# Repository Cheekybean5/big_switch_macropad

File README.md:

# Big_Switch_Pad

BIG SWITCH MACROPAD is a custom macropad featuring a 2×4 cluster of ISO Enter keys stacked above a 1×6 row of 1u keys. Looming over the layout is a Kailh Big Switch that serves as the visual and functional centerpiece of the board. The pad runs QMK Firmware and is powered by an RP2040 microcontroller.

## Features:

- KAILH BIG SWITCH

- 8 x ISO ENTER Keys

- 6 x 1u Keys

- QMK Firmware

- 3d Printed Case

## CAD Model:

The main case section fits together using M3 x 16mm bolts and M3x5mmx4mm heatset inserts. 
The big switch housing is connected to main body using 6mm Diameter x 1.5mm magnets.

Here are some renders of the assembled case:

Case designed in Fusion360.

## PCB

PCB designed in KiCad. The Diode and Through-hole near the top must be handwired to the big switch.

Schematic:

PCB:

## Firmware

This project utilizes [QMK](https://qmk.fm/) firmware.

Here is the Default Keymap and Keycodes Assigned to it:

- The Big Switch acts as a large "off button" and is wired into the Matrix

## BOM:

Here is the list of parts required for this project:

- 14x Cherry MX switches

- 1x Kailh Big Switch (available at Novelkeys)

- 6x 1u Keycaps (any profile)

- 8x ISO Enter Keys

- 8x 2u Stabilizers (Semi-optional)

- 1x Seeed XIAO RP2040

- 2x Hookup Wire Segments (Approx. 6 inches each)

- 4x 6mm Diameter x 1.5mm Height Magnets

- 15x Through-hole 1N4148 Diodes

-  M3x16mm bolts

- M3x5mx4mm heatset inserts

- 1x Case (3 printed parts)

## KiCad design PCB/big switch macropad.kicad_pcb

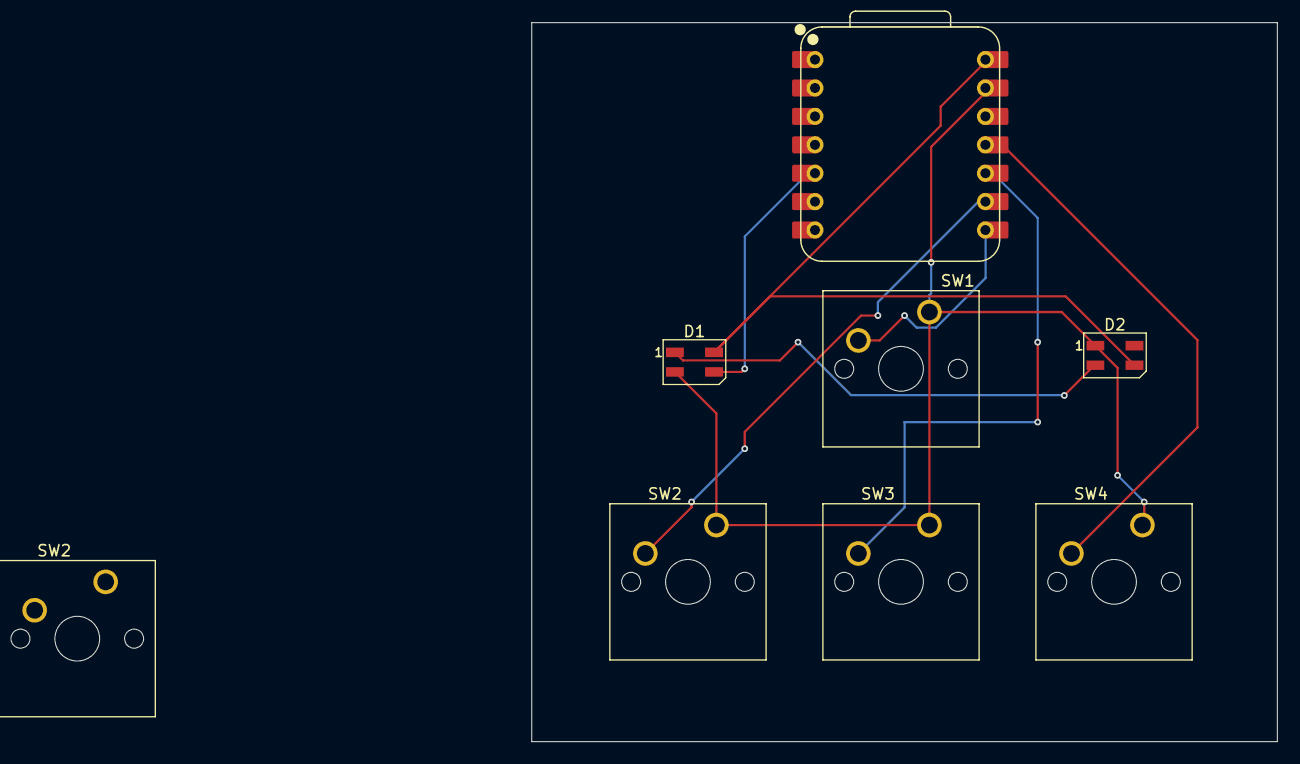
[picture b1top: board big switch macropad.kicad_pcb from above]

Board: 2 copper layers, 66.7 x 64.3 mm, 8 parts (0 on the bottom side), 8 nets.

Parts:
D1: SK6812MINI; LED_SK6812MINI_PLCC4_3.5x3.5mm_P1.75mm
D2: SK6812; LED_SK6812MINI_PLCC4_3.5x3.5mm_P1.75mm
SW1, SW2, SW2#2, SW3, SW4: SW_Push; SW_Cherry_MX_1.00u_PCB
U1: XIAO-RP2040-DIP

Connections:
+5V: D1.4 (VDD), D2.3 (VDD), U1.14 (VBUS)
GND: D1.2 (VSS), D2.1 (VSS), SW1.1, SW2#2.1, SW3.1, SW4.1, U1.13 (GND)
unnamed: D1.3 (DIN), U1.5 (GPIO6/SDA)
unnamed: D1.1 (DOUT), D2.2 (DIN)
unnamed: SW1.2, U1.8 (GPIO1/RX)
unnamed: SW2#2.2, U1.9 (GPIO2/SCK)
unnamed: SW4.2, U1.11 (GPIO3/MOSI)
unnamed: SW3.2, U1.10 (GPIO4/MISO)

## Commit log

2026-01-19 Add initial files
2026-01-19 Add default keymap image
    for readme
2026-01-19 Rename Default Keymap Assignments.png to default_keymap_assignments
2026-01-19 Rename pcb editor.png to pcb_editor.png
2026-01-19 Rename default_keymap_assignments to default_keymap_assignments.png
